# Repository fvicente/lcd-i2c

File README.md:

# lcd-i2c
Yet another conversor board for generic 16x2 line displays to I2C

http://www.alfersoft.com.ar/blog/2013/04/05/yet-another-conversor-board-for-generic-16x2-line-displays-to-i2c/

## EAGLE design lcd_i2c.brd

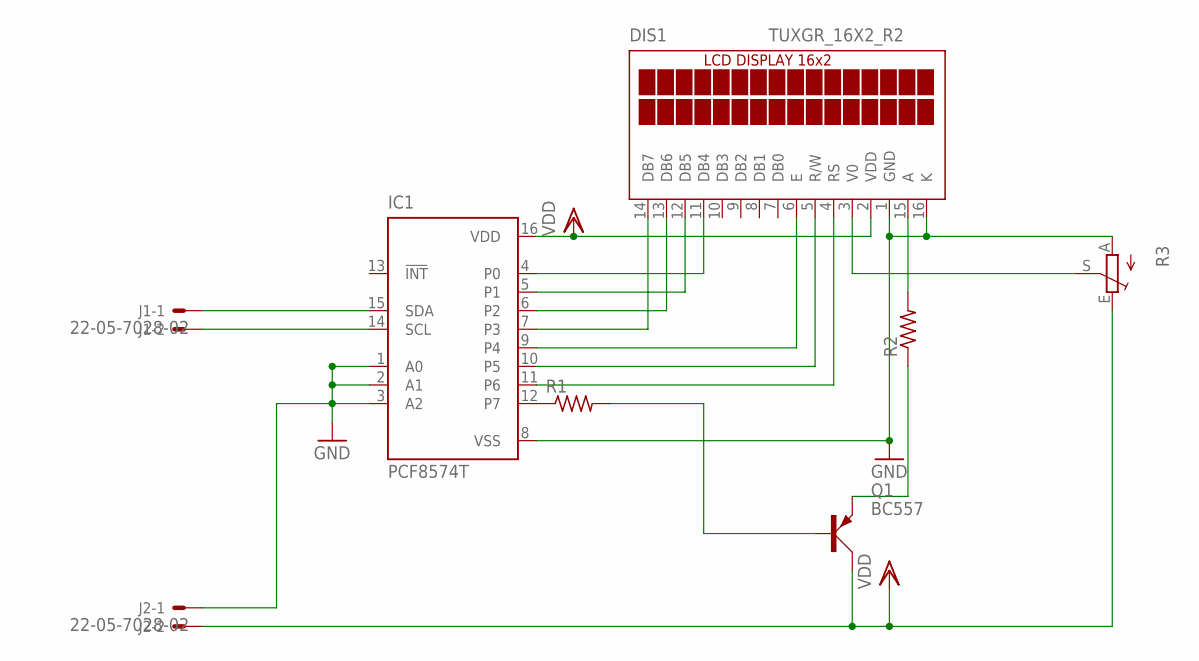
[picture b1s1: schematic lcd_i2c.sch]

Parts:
DIS1: TUXGR_16X2_R2
IC1: PCF8574T; SO16W
J1, J2: 22-05-7028-02; 7395-02
Q1: BC557; SOT54A
R1, R2: R-US_0207/7; 0207/7
R3: TRIM_EU-B25X; B25X

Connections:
GND: DIS1.1 (GND), DIS1.16 (K), IC1.1 (A0), IC1.2 (A1), IC1.3 (A2), IC1.8 (VSS), J2.1, R3.A
unnamed: DIS1.15 (A), R2.2
unnamed: DIS1.3 (V0), R3.S
unnamed: DIS1.11 (DB4), IC1.4 (P0)
unnamed: DIS1.12 (DB5), IC1.5 (P1)
unnamed: DIS1.13 (DB6), IC1.6 (P2)
unnamed: DIS1.14 (DB7), IC1.7 (P3)
unnamed: DIS1.6 (E), IC1.9 (P4)
unnamed: DIS1.5 (R/W), IC1.10 (P5)
unnamed: DIS1.4 (RS), IC1.11 (P6)
unnamed: IC1.12 (P7), R1.1
unnamed: Q1.E, R2.1
unnamed: IC1.14 (SCL), J1.2
unnamed: Q1.B, R1.2
unnamed: IC1.15 (SDA), J1.1
VDD: DIS1.2 (VDD), IC1.16 (VDD), J2.2, Q1.C, R3.E

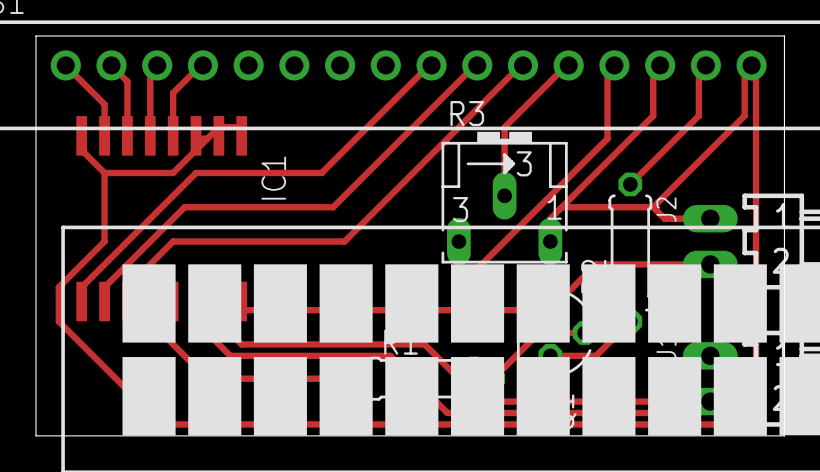
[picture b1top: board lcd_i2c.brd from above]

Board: 1 copper layer, 41.6 x 22.2 mm, 8 parts (0 on the bottom side), 16 nets.
